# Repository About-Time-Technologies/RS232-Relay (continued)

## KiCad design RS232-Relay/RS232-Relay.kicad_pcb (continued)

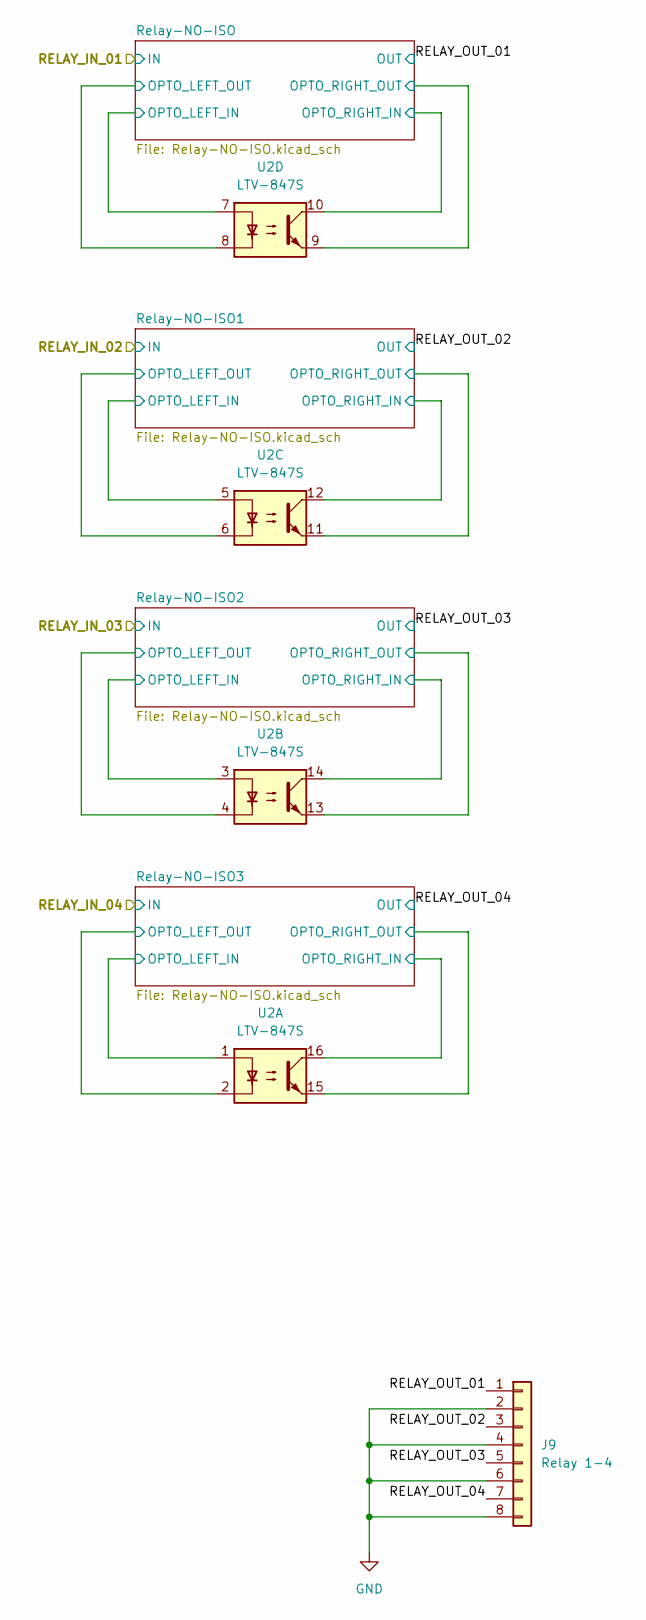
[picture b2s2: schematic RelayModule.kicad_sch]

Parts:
J9: Relay 1-4; PhoenixContact_MSTBA_2,5_8-G-5,08_1x08_P5.08mm_Horizontal
U2: LTV-847S; SMDIP-16_W9.53mm

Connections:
+12V: U2.10, U2.12, U2.14, U2.16; also elsewhere on the board
/Relay-Module/RELAY_OUT_01: J9.1; also elsewhere on the board
/Relay-Module/RELAY_OUT_02: J9.3; also elsewhere on the board
/Relay-Module/RELAY_OUT_03: J9.5; also elsewhere on the board
/Relay-Module/RELAY_OUT_04: J9.7; also elsewhere on the board
/Relay-Module/Relay-NO-ISO1/OPTO_LEFT_IN: U2.5; also elsewhere on the board
/Relay-Module/Relay-NO-ISO1/OPTO_RIGHT_OUT: U2.11; also elsewhere on the board
/Relay-Module/Relay-NO-ISO2/OPTO_LEFT_IN: U2.3; also elsewhere on the board
/Relay-Module/Relay-NO-ISO2/OPTO_RIGHT_OUT: U2.13; also elsewhere on the board
/Relay-Module/Relay-NO-ISO3/OPTO_LEFT_IN: U2.1; also elsewhere on the board
/Relay-Module/Relay-NO-ISO3/OPTO_RIGHT_OUT: U2.15; also elsewhere on the board
/Relay-Module/Relay-NO-ISO/OPTO_LEFT_IN: U2.7; also elsewhere on the board
/Relay-Module/Relay-NO-ISO/OPTO_RIGHT_OUT: U2.9; also elsewhere on the board
GND: J9.2, J9.4, J9.6, J9.8; also elsewhere on the board
RELAY_IN_01: U2.8; also elsewhere on the board
RELAY_IN_02: U2.6; also elsewhere on the board
RELAY_IN_03: U2.4; also elsewhere on the board
RELAY_IN_04: U2.2; also elsewhere on the board

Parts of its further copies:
J10, J11: Relay 1-4; PhoenixContact_MSTBA_2,5_8-G-5,08_1x08_P5.08mm_Horizontal
U5, U6: LTV-847S; SMDIP-16_W9.53mm

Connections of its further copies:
+12V: U5.10, U5.12, U5.14, U5.16, U6.10, U6.12, U6.14, U6.16; also elsewhere on the board
/Relay-Module1/RELAY_OUT_01: J10.1; also elsewhere on the board
/Relay-Module1/RELAY_OUT_02: J10.3; also elsewhere on the board
/Relay-Module1/RELAY_OUT_03: J10.5; also elsewhere on the board
/Relay-Module1/RELAY_OUT_04: J10.7; also elsewhere on the board
/Relay-Module1/Relay-NO-ISO1/OPTO_LEFT_IN: U5.5; also elsewhere on the board
/Relay-Module1/Relay-NO-ISO1/OPTO_RIGHT_OUT: U5.11; also elsewhere on the board
/Relay-Module1/Relay-NO-ISO2/OPTO_LEFT_IN: U5.3; also elsewhere on the board
/Relay-Module1/Relay-NO-ISO2/OPTO_RIGHT_OUT: U5.13; also elsewhere on the board
/Relay-Module1/Relay-NO-ISO3/OPTO_LEFT_IN: U5.1; also elsewhere on the board
/Relay-Module1/Relay-NO-ISO3/OPTO_RIGHT_OUT: U5.15; also elsewhere on the board
/Relay-Module1/Relay-NO-ISO/OPTO_LEFT_IN: U5.7; also elsewhere on the board
/Relay-Module1/Relay-NO-ISO/OPTO_RIGHT_OUT: U5.9; also elsewhere on the board
/Relay-Module2/RELAY_OUT_01: J11.1; also elsewhere on the board
/Relay-Module2/RELAY_OUT_02: J11.3; also elsewhere on the board
/Relay-Module2/RELAY_OUT_03: J11.5; also elsewhere on the board
/Relay-Module2/RELAY_OUT_04: J11.7; also elsewhere on the board
/Relay-Module2/Relay-NO-ISO1/OPTO_LEFT_IN: U6.5; also elsewhere on the board
/Relay-Module2/Relay-NO-ISO1/OPTO_RIGHT_OUT: U6.11; also elsewhere on the board
/Relay-Module2/Relay-NO-ISO2/OPTO_LEFT_IN: U6.3; also elsewhere on the board
/Relay-Module2/Relay-NO-ISO2/OPTO_RIGHT_OUT: U6.13; also elsewhere on the board
/Relay-Module2/Relay-NO-ISO3/OPTO_LEFT_IN: U6.1; also elsewhere on the board
/Relay-Module2/Relay-NO-ISO3/OPTO_RIGHT_OUT: U6.15; also elsewhere on the board
/Relay-Module2/Relay-NO-ISO/OPTO_LEFT_IN: U6.7; also elsewhere on the board
/Relay-Module2/Relay-NO-ISO/OPTO_RIGHT_OUT: U6.9; also elsewhere on the board
GND: J10.2, J10.4, J10.6, J10.8, J11.2, J11.4, J11.6, J11.8; also elsewhere on the board
RELAY_IN_05: U5.8; also elsewhere on the board
RELAY_IN_06: U5.6; also elsewhere on the board
RELAY_IN_07: U5.4; also elsewhere on the board
RELAY_IN_08: U5.2; also elsewhere on the board
RELAY_IN_09: U6.8; also elsewhere on the board
RELAY_IN_10: U6.6; also elsewhere on the board
RELAY_IN_11: U6.4; also elsewhere on the board
RELAY_IN_12: U6.2; also elsewhere on the board

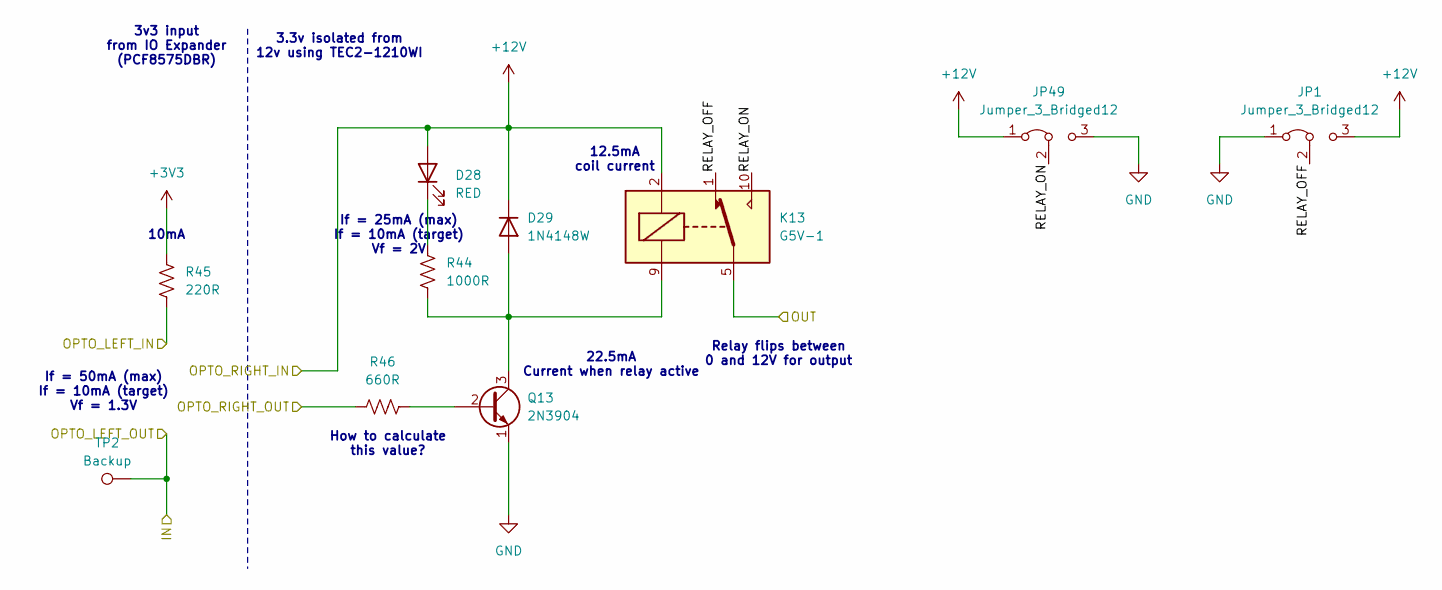
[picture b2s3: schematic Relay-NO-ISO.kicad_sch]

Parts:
D28: RED; LED_0805_2012Metric; LCSC C84256
D29: 1N4148W; D_SOD-123; LCSC C2099
JP1, JP49: Jumper_3_Bridged12; SolderJumper-3_P1.3mm_Bridged2Bar12_RoundedPad1.0x1.5mm
K13: G5V-1; Relay_SPDT_Omron_G5V-1
Q13: 2N3904; SOT-23; LCSC C20526
R44: 1000R; R_0603_1608Metric; LCSC C21190
R45: 220R; R_0603_1608Metric; LCSC C22962
R46: 660R; R_0603_1608Metric; LCSC C21189
TP2: Backup; TestPoint_Pad_D1.0mm

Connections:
+3V3: R45.2; also elsewhere on the board
+12V: D28.2 (A), D29.1 (K), JP1.3 (B), JP49.1 (A), K13.2; also elsewhere on the board
/Relay-Module/RELAY_OUT_01: K13.5, K13.6; also elsewhere on the board
/Relay-Module/Relay-NO-ISO/OPTO_LEFT_IN: R45.1; also elsewhere on the board
/Relay-Module/Relay-NO-ISO/OPTO_RIGHT_OUT: R46.1; also elsewhere on the board
/Relay-Module/Relay-NO-ISO/RELAY_OFF: JP1.2 (C), K13.1
/Relay-Module/Relay-NO-ISO/RELAY_ON: JP49.2 (C), K13.10
GND: JP1.1 (A), JP49.3 (B), Q13.1 (E); also elsewhere on the board
unnamed: D28.1 (K), R44.1
unnamed: D29.2 (A), K13.9, Q13.3 (C), R44.2
unnamed: Q13.2 (B), R46.2
RELAY_IN_01: TP2.1; also elsewhere on the board

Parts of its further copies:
D1, D3, D8, D10, D12, D14, D16, D18, D20, D30, D32: RED; LED_0805_2012Metric; LCSC C84256
D2, D4, D9, D11, D13, D15, D17, D19, D21, D31, D33: 1N4148W; D_SOD-123; LCSC C2099
JP2, JP3, JP4, JP5, JP6, JP7, JP8, JP9, JP10, JP11, JP12, JP50, JP51, JP52, JP53, JP54, JP55, JP56, JP57, JP58, JP59, JP60: Jumper_3_Bridged12; SolderJumper-3_P1.3mm_Bridged2Bar12_RoundedPad1.0x1.5mm
K1, K2, K3, K4, K5, K6, K7, K8, K9, K14, K15: G5V-1; Relay_SPDT_Omron_G5V-1
Q1, Q2, Q3, Q4, Q5, Q6, Q7, Q8, Q9, Q14, Q15: 2N3904; SOT-23; LCSC C20526
R2, R11, R14, R17, R20, R23, R26, R29, R32, R47, R50: 1000R; R_0603_1608Metric; LCSC C21190
R3, R12, R15, R18, R21, R24, R27, R30, R33, R48, R51: 220R; R_0603_1608Metric; LCSC C22962
R5, R13, R16, R19, R22, R25, R28, R31, R34, R49, R52: 660R; R_0603_1608Metric; LCSC C21189
TP3, TP14, TP15, TP16, TP17, TP18, TP19, TP20, TP21, TP22, TP23: Backup; TestPoint_Pad_D1.0mm

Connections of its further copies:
+3V3: R3.2, R12.2, R15.2, R18.2, R21.2, R24.2, R27.2, R30.2, R33.2, R48.2, R51.2; also elsewhere on the board
+12V: D1.2 (A), D2.1 (K), D3.2 (A), D4.1 (K), D8.2 (A), D9.1 (K), D10.2 (A), D11.1 (K), D12.2 (A), D13.1 (K), D14.2 (A), D15.1 (K), D16.2 (A), D17.1 (K), D18.2 (A), D19.1 (K), D20.2 (A), D21.1 (K), D30.2 (A), D31.1 (K), D32.2 (A), D33.1 (K), JP2.3 (B), JP3.3 (B), JP4.3 (B), JP5.3 (B), JP6.3 (B), JP7.3 (B), JP8.3 (B), JP9.3 (B), JP10.3 (B), JP11.3 (B), JP12.3 (B), JP50.1 (A), JP51.1 (A), JP52.1 (A), JP53.1 (A), JP54.1 (A), JP55.1 (A), JP56.1 (A), JP57.1 (A), JP58.1 (A), JP59.1 (A), JP60.1 (A), K1.2, K2.2, K3.2, K4.2, K5.2, K6.2, K7.2, K8.2, K9.2, K14.2, K15.2; also elsewhere on the board
/Relay-Module1/RELAY_OUT_01: K14.5, K14.6; also elsewhere on the board
/Relay-Module1/RELAY_OUT_02: K2.5, K2.6; also elsewhere on the board
/Relay-Module1/RELAY_OUT_03: K5.5, K5.6; also elsewhere on the board
/Relay-Module1/RELAY_OUT_04: K8.5, K8.6; also elsewhere on the board
/Relay-Module1/Relay-NO-ISO1/OPTO_LEFT_IN: R12.1; also elsewhere on the board
/Relay-Module1/Relay-NO-ISO1/OPTO_RIGHT_OUT: R13.1; also elsewhere on the board
/Relay-Module1/Relay-NO-ISO1/RELAY_OFF: JP5.2 (C), K2.1
/Relay-Module1/Relay-NO-ISO1/RELAY_ON: JP53.2 (C), K2.10
/Relay-Module1/Relay-NO-ISO2/OPTO_LEFT_IN: R21.1; also elsewhere on the board
/Relay-Module1/Relay-NO-ISO2/OPTO_RIGHT_OUT: R22.1; also elsewhere on the board
/Relay-Module1/Relay-NO-ISO2/RELAY_OFF: JP8.2 (C), K5.1
/Relay-Module1/Relay-NO-ISO2/RELAY_ON: JP56.2 (C), K5.10
/Relay-Module1/Relay-NO-ISO3/OPTO_LEFT_IN: R30.1; also elsewhere on the board
/Relay-Module1/Relay-NO-ISO3/OPTO_RIGHT_OUT: R31.1; also elsewhere on the board
/Relay-Module1/Relay-NO-ISO3/RELAY_OFF: JP11.2 (C), K8.1
/Relay-Module1/Relay-NO-ISO3/RELAY_ON: JP59.2 (C), K8.10
/Relay-Module1/Relay-NO-ISO/OPTO_LEFT_IN: R48.1; also elsewhere on the board
/Relay-Module1/Relay-NO-ISO/OPTO_RIGHT_OUT: R49.1; also elsewhere on the board
/Relay-Module1/Relay-NO-ISO/RELAY_OFF: JP2.2 (C), K14.1
/Relay-Module1/Relay-NO-ISO/RELAY_ON: JP50.2 (C), K14.10
/Relay-Module2/RELAY_OUT_01: K15.5, K15.6; also elsewhere on the board
/Relay-Module2/RELAY_OUT_02: K3.5, K3.6; also elsewhere on the board
/Relay-Module2/RELAY_OUT_03: K6.5, K6.6; also elsewhere on the board
/Relay-Module2/RELAY_OUT_04: K9.5, K9.6; also elsewhere on the board
/Relay-Module2/Relay-NO-ISO1/OPTO_LEFT_IN: R15.1; also elsewhere on the board
/Relay-Module2/Relay-NO-ISO1/OPTO_RIGHT_OUT: R16.1; also elsewhere on the board
/Relay-Module2/Relay-NO-ISO1/RELAY_OFF: JP6.2 (C), K3.1
/Relay-Module2/Relay-NO-ISO1/RELAY_ON: JP54.2 (C), K3.10
/Relay-Module2/Relay-NO-ISO2/OPTO_LEFT_IN: R24.1; also elsewhere on the board
/Relay-Module2/Relay-NO-ISO2/OPTO_RIGHT_OUT: R25.1; also elsewhere on the board
/Relay-Module2/Relay-NO-ISO2/RELAY_OFF: JP9.2 (C), K6.1
/Relay-Module2/Relay-NO-ISO2/RELAY_ON: JP57.2 (C), K6.10
/Relay-Module2/Relay-NO-ISO3/OPTO_LEFT_IN: R33.1; also elsewhere on the board
/Relay-Module2/Relay-NO-ISO3/OPTO_RIGHT_OUT: R34.1; also elsewhere on the board
/Relay-Module2/Relay-NO-ISO3/RELAY_OFF: JP12.2 (C), K9.1
/Relay-Module2/Relay-NO-ISO3/RELAY_ON: JP60.2 (C), K9.10
/Relay-Module2/Relay-NO-ISO/OPTO_LEFT_IN: R51.1; also elsewhere on the board
/Relay-Module2/Relay-NO-ISO/OPTO_RIGHT_OUT: R52.1; also elsewhere on the board
/Relay-Module2/Relay-NO-ISO/RELAY_OFF: JP3.2 (C), K15.1
/Relay-Module2/Relay-NO-ISO/RELAY_ON: JP51.2 (C), K15.10
/Relay-Module/RELAY_OUT_02: K1.5, K1.6; also elsewhere on the board
/Relay-Module/RELAY_OUT_03: K4.5, K4.6; also elsewhere on the board
/Relay-Module/RELAY_OUT_04: K7.5, K7.6; also elsewhere on the board
/Relay-Module/Relay-NO-ISO1/OPTO_LEFT_IN: R3.1; also elsewhere on the board
/Relay-Module/Relay-NO-ISO1/OPTO_RIGHT_OUT: R5.1; also elsewhere on the board
/Relay-Module/Relay-NO-ISO1/RELAY_OFF: JP4.2 (C), K1.1
/Relay-Module/Relay-NO-ISO1/RELAY_ON: JP52.2 (C), K1.10
/Relay-Module/Relay-NO-ISO2/OPTO_LEFT_IN: R18.1; also elsewhere on the board
/Relay-Module/Relay-NO-ISO2/OPTO_RIGHT_OUT: R19.1; also elsewhere on the board
/Relay-Module/Relay-NO-ISO2/RELAY_OFF: JP7.2 (C), K4.1
/Relay-Module/Relay-NO-ISO2/RELAY_ON: JP55.2 (C), K4.10
/Relay-Module/Relay-NO-ISO3/OPTO_LEFT_IN: R27.1; also elsewhere on the board
/Relay-Module/Relay-NO-ISO3/OPTO_RIGHT_OUT: R28.1; also elsewhere on the board
/Relay-Module/Relay-NO-ISO3/RELAY_OFF: JP10.2 (C), K7.1
/Relay-Module/Relay-NO-ISO3/RELAY_ON: JP58.2 (C), K7.10
GND: JP2.1 (A), JP3.1 (A), JP4.1 (A), JP5.1 (A), JP6.1 (A), JP7.1 (A), JP8.1 (A), JP9.1 (A), JP10.1 (A), JP11.1 (A), JP12.1 (A), JP50.3 (B), JP51.3 (B), JP52.3 (B), JP53.3 (B), JP54.3 (B), JP55.3 (B), JP56.3 (B), JP57.3 (B), JP58.3 (B), JP59.3 (B), JP60.3 (B), Q1.1 (E), Q2.1 (E), Q3.1 (E), Q4.1 (E), Q5.1 (E), Q6.1 (E), Q7.1 (E), Q8.1 (E), Q9.1 (E), Q14.1 (E), Q15.1 (E); also elsewhere on the board
unnamed: D1.1 (K), R2.1
unnamed: D2.2 (A), K1.9, Q1.3 (C), R2.2
unnamed: D3.1 (K), R11.1
unnamed: D4.2 (A), K2.9, Q2.3 (C), R11.2
unnamed: D8.1 (K), R14.1
unnamed: D9.2 (A), K3.9, Q3.3 (C), R14.2
unnamed: D10.1 (K), R17.1
unnamed: D11.2 (A), K4.9, Q4.3 (C), R17.2
unnamed: D12.1 (K), R20.1
unnamed: D13.2 (A), K5.9, Q5.3 (C), R20.2
unnamed: D14.1 (K), R23.1
unnamed: D15.2 (A), K6.9, Q6.3 (C), R23.2
unnamed: D16.1 (K), R26.1
unnamed: D17.2 (A), K7.9, Q7.3 (C), R26.2
unnamed: D18.1 (K), R29.1
unnamed: D19.2 (A), K8.9, Q8.3 (C), R29.2
unnamed: D20.1 (K), R32.1
unnamed: D21.2 (A), K9.9, Q9.3 (C), R32.2
unnamed: D30.1 (K), R47.1
unnamed: D31.2 (A), K14.9, Q14.3 (C), R47.2
unnamed: D32.1 (K), R50.1
unnamed: D33.2 (A), K15.9, Q15.3 (C), R50.2
unnamed: Q1.2 (B), R5.2
unnamed: Q2.2 (B), R13.2
unnamed: Q3.2 (B), R16.2
unnamed: Q4.2 (B), R19.2
unnamed: Q5.2 (B), R22.2
unnamed: Q6.2 (B), R25.2
unnamed: Q7.2 (B), R28.2
unnamed: Q8.2 (B), R31.2
unnamed: Q9.2 (B), R34.2
unnamed: Q14.2 (B), R49.2
unnamed: Q15.2 (B), R52.2
RELAY_IN_02: TP15.1; also elsewhere on the board
RELAY_IN_03: TP18.1; also elsewhere on the board
RELAY_IN_04: TP21.1; also elsewhere on the board
RELAY_IN_05: TP3.1; also elsewhere on the board
RELAY_IN_06: TP16.1; also elsewhere on the board
RELAY_IN_07: TP19.1; also elsewhere on the board
RELAY_IN_08: TP22.1; also elsewhere on the board
RELAY_IN_09: TP14.1; also elsewhere on the board
RELAY_IN_10: TP17.1; also elsewhere on the board
RELAY_IN_11: TP20.1; also elsewhere on the board
RELAY_IN_12: TP23.1; also elsewhere on the board

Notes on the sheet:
12.5mA coil current
10mA
3.3v isolated from 12v using TEC2-1210WI
Relay flips between 0 and 12V for output
If = 50mA (max) If = 10mA (target) Vf = 1.3V
How to calculate this value?
22.5mA Current when relay active
3v3 input from IO Expander (PCF8575DBR)
If = 25mA (max) If = 10mA (target) Vf = 2V

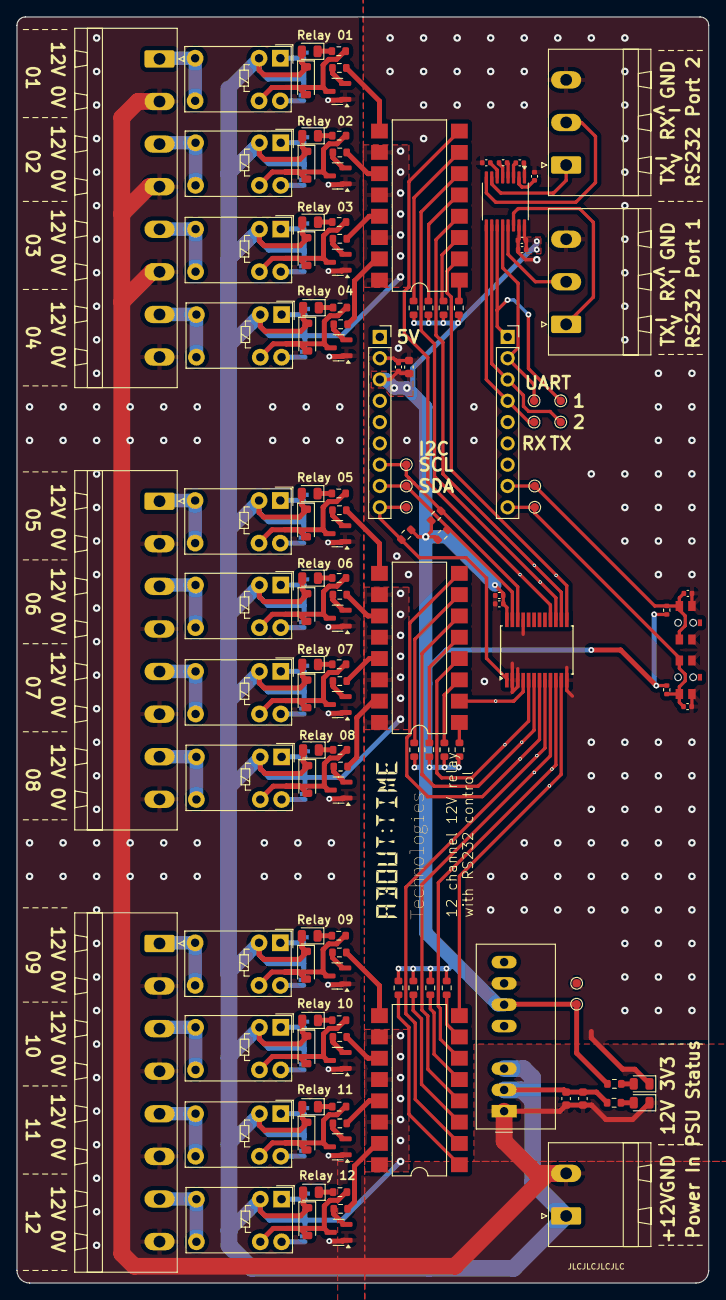
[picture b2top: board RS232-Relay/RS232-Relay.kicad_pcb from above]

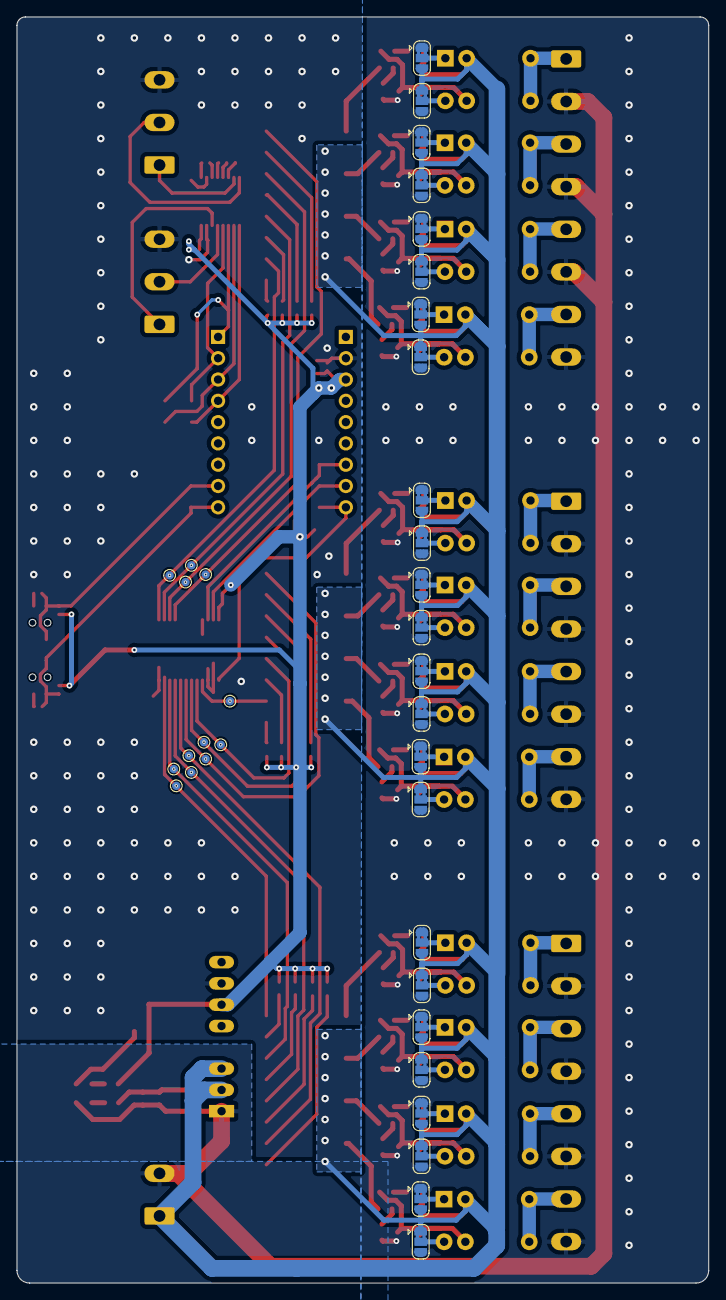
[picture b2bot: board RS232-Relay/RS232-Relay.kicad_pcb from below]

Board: 2 copper layers, 82.5 x 151.0 mm, 170 parts (36 on the bottom side), 133 nets.

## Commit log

2024-08-26 Relay layout
2024-08-27 Including ESP32
2024-08-28 Adding RS232
2024-09-01 Basic schematic fully complete
2024-09-01 Fixing pin headers
2024-09-01 Schematic complete
2024-09-01 Pre-template layouts
2024-09-01 1x Layout Complete
2024-09-01 Routing Complete (vias next)
2024-09-02 Initial fabrication samples
2024-09-02 Port labels
2024-09-02 Hide silkscreen designators
2024-09-03 Silkscreen finished and vias added
2024-09-03 Switching to drain rather than source
2024-09-10 Figuring out the relay NC/NO connections
2024-09-10 Figured out a solution, now for implementation
2024-09-10 Solution implemented
2024-09-10 50Ohm -> 51Ohm resistor on LED
2024-09-11 Production v1
2024-09-13 Auto stash before merge of "main" and "origin/main"
2024-09-13 PCB 3D Model for Blender testing
2024-09-14 Initial UART gambit
2024-09-15 Base code for RS232 command format
2024-09-15 Migration
2024-09-21 Pre-arduino
2024-09-27 Reverting to a really simple codebase
2024-09-27 Transitioning to more robust circuit
2024-10-06 It could work but it's too big
2024-10-06 Schematic ready
2024-10-10 Blinking LED
2024-10-13 Update .gitignore for source directory
2024-10-13 Clean out src
2024-10-13 Managed components removed
2024-10-13 Rename files and tidy up
2024-10-26 UART configuration
2024-10-30 Code functional
2024-12-27 Python Integration Testing
2025-03-02 Add relay query commands to each request
